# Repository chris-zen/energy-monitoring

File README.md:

# energy-monitoring

Source for my home's energy monitoring system

- [arduino](arduino) contains the firmware for an Arduino UNO board that samples voltage and intensity signals. Sampled data can be transferred to the computer through the USB port as a serial device.
- [python](python) contains Python code that knows how to read voltage and intensity data sampled with the Arduino board, how to filter and process the data to calculate Volts, Intensity and Power, and generate plots with [matplotlib](https://matplotlib.org/).
- [eagle](eagle) contains a hardware design for the final energy monitoring system, including the analog stages to prepare voltage and intensity signals to be sampled by the Arduino ADC (Unfinished).

# Blogs

* [My home energy monitoring vision](https://aloneinthehack.wordpress.com/2013/05/20/my-home-energy-monitoring-vision/)
* [First power measurements](https://aloneinthehack.wordpress.com/2013/04/27/first-power-measurements/)
* [Starting to explore OpenEnergyMonitor.org](https://aloneinthehack.wordpress.com/2013/04/07/starting-to-explore-openenergymonitor-org/)

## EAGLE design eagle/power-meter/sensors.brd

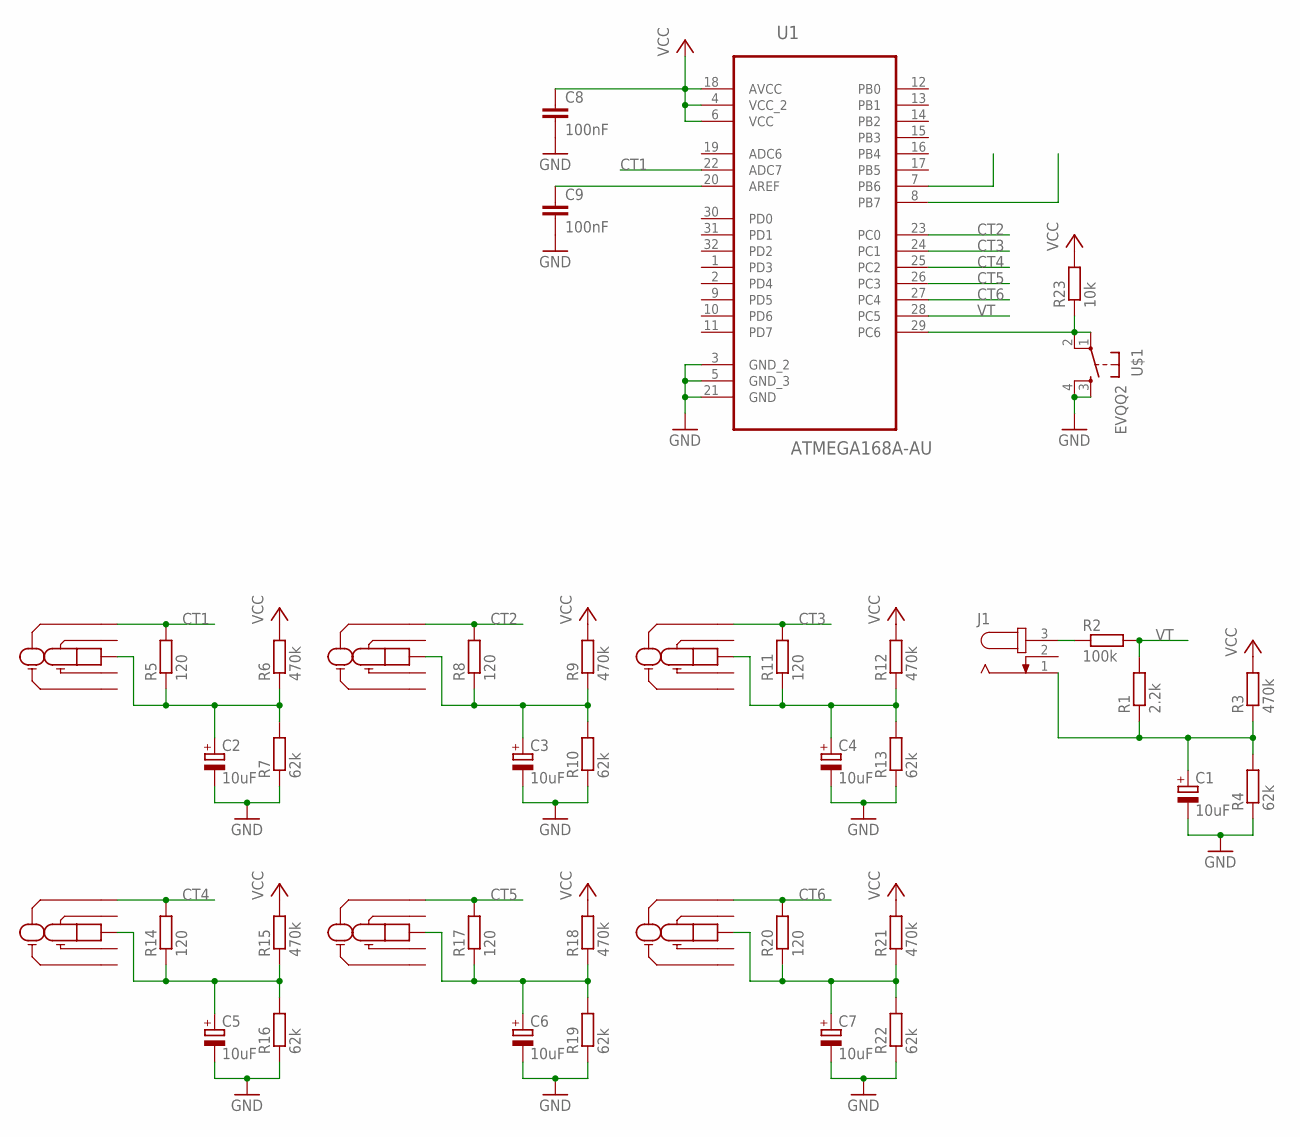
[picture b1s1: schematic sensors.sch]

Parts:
C1, C2, C3, C4, C5, C6, C7: 10uF; 153CLV-0405
C8, C9: 100nF; C1206
J1: JACK-PLUG0; SPC4077
JC1: 15428/BT
JC2, JC3, JC4, JC5, JC6: 15428/BT; 15428/BT@1
R1: 2.2k; R1206
R2: 100k; R1206
R3, R6, R9, R12, R15, R18, R21: 470k; R1206
R4, R7, R10, R13, R16, R19, R22: 62k; R1206
R5, R8, R11, R14, R17, R20: 120; R1206
R23: 10k; R1206
U1: ATMEGA168A-AU; QFP80P900X900X120-32N
U$1: EVQQ2

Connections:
AREF: C9.1, U1.20 (AREF)
CT1: JC1.P2, R5.2, U1.22 (ADC7)
CT2: JC2.P2, R8.2, U1.23 (PC0)
CT3: JC3.P2, R11.2, U1.24 (PC1)
CT4: JC4.P2, R14.2, U1.25 (PC2)
CT5: JC5.P2, R17.2, U1.26 (PC3)
CT6: JC6.P2, R20.2, U1.27 (PC4)
GND: C1.-, C2.-, C3.-, C4.-, C5.-, C6.-, C7.-, C8.2, C9.2, R4.1, R7.1, R10.1, R13.1, R16.1, R19.1, R22.1, U1.3 (GND_2), U1.5 (GND_3), U1.21 (GND), U$1.3, U$1.4
unnamed: J1.3, R2.1
unnamed: C1.+, J1.1, R1.1, R3.1, R4.2
unnamed: C2.+, JC1.P1, R5.1, R6.1, R7.2
unnamed: C3.+, JC2.P1, R8.1, R9.1, R10.2
unnamed: C4.+, JC3.P1, R11.1, R12.1, R13.2
unnamed: C5.+, JC4.P1, R14.1, R15.1, R16.2
unnamed: C6.+, JC5.P1, R17.1, R18.1, R19.2
unnamed: C7.+, JC6.P1, R20.1, R21.1, R22.2
RESET: R23.1, U1.29 (PC6), U$1.1, U$1.2
VCC: C8.1, R3.2, R6.2, R9.2, R12.2, R15.2, R18.2, R21.2, R23.2, U1.4 (VCC_2), U1.6 (VCC), U1.18 (AVCC)
VT: R1.2, R2.2, U1.28 (PC5)

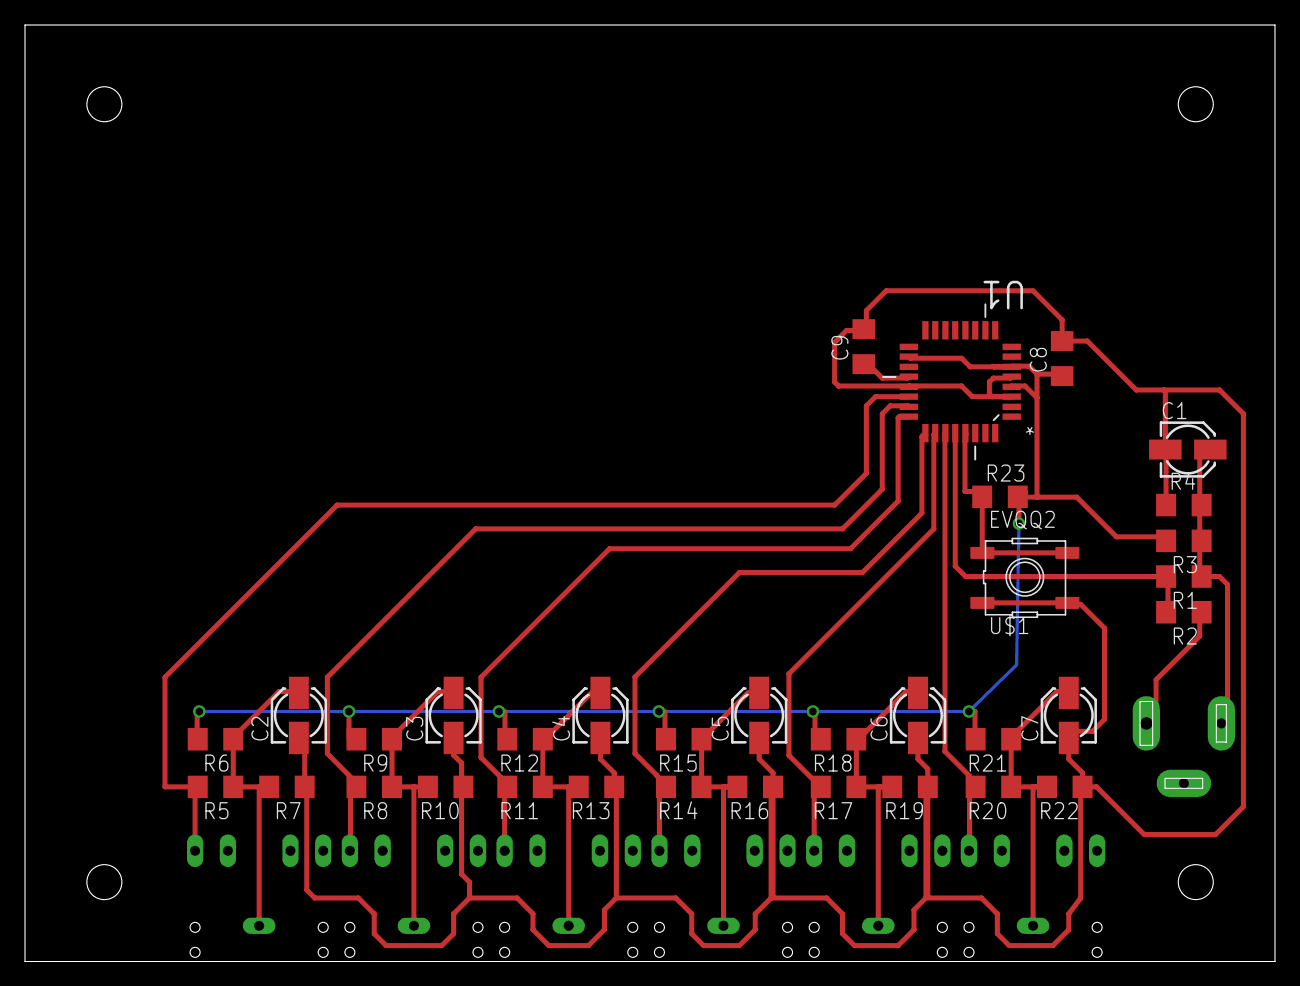
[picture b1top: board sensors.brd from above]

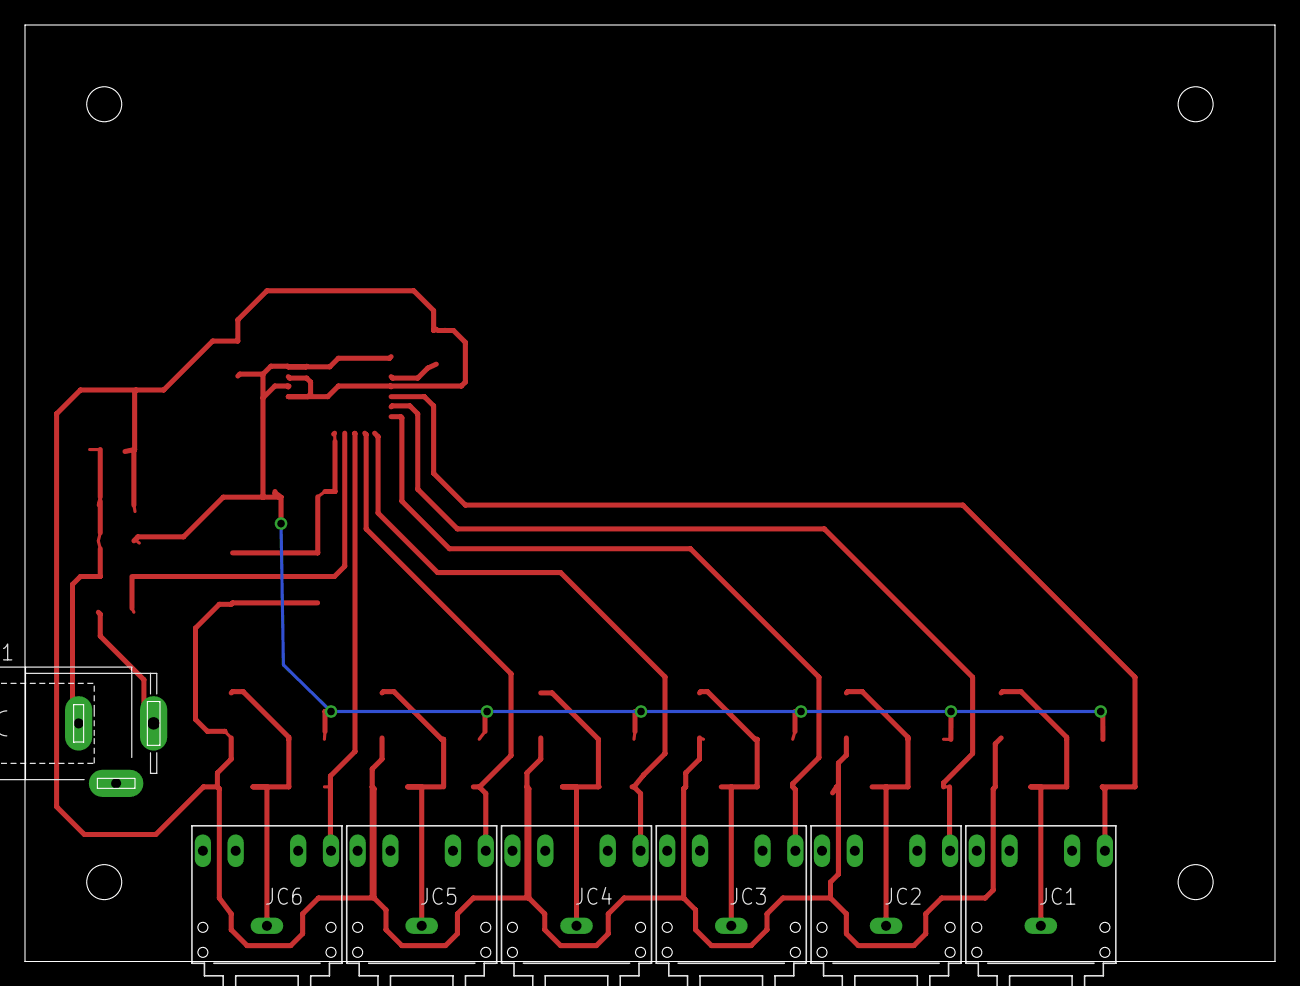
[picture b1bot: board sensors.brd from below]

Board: 2 copper layers, 100.0 x 74.9 mm, 41 parts (7 on the bottom side), 19 nets.

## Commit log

2013-04-23 Initial code
2013-04-27 Small changes in power_scope for video recording
2013-04-28 Build using a makefile
2013-04-28 Modularizing sampler.ino
2013-05-03 arduino power node started
2013-05-03 power calculation works
2013-05-05 Power Analyzer created
2013-05-25 Fixed a bug with last value in lp and hp filters in signalv
2013-05-25 Sampler adapted to work with reference voltage of 1.1V
2013-05-25 plot_score works with reference voltage of 1.1V and shows ADV input voltage instead of steps
2013-05-25 Working on the power-meter schemas
2013-06-04 Common Eagle library created. Working on power-node schematics
2013-06-10 Working on power-monitor PCB
